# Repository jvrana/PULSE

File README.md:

# PULSE

## Opensource LED pulser for optogenetic applications

This repo provides instructions for building an inexpensive and open-sourced LED pulser for optogenetic applications. The pulser is a multi-output, programmable LED light device. 

IMAGE OF INTERFACE

IMAGE OF IT IN ACTION

IMAGE OF IT BEING BUILT

Service: ...message about contact...

/*
 @author: Justin D Vrana
 @version v2.32
 @since 2014-04-03

What is this?
The basic code needed to control a multi-output, programmable LED light device for optogenetic applications. 
The the code allows for user-defined parameters to alter duration and intensity of light pulses at regular intervals.  
Central to the device is an inexpensive microcontroller and LCD keypad to display and read user input to control 
the duration and intensity of LED light pulses at user-defined intervals. Up to three LED outputs can be independently
programmed and different LED modules can be interchanged.

Usage:
Upload to Arduino Uno via USB. If uploaded properly, "Starting" should display on the LCD display screen and then the main page should display.
If there are issue uploading to the Arduino Uno, consult the Arduino website for help.
    
    To turn an output ON or OFF: From the main page on the LCD display, use the UP and DOWN buttons to select an output (indicated by a cursor)
    to edit. Move the cursor to the right using the RIGHT button and use either the UP or DOWN button to turn the output program ON
    or OFF. A countdown timer which counts down untill the next time the LED is to flash will display when the output program is running. 
    
    To change an output's scheduled flashing: To change an output program, push SELECT to select the output highlighted by the cursor. 
    Use the UP and DOWN buttons to select and attribute to edit. To edit and attribute, move the cursor to the right using the RIGHT
    button and then hold the UP or DOWN button to increase or decease a value. Move the cursor back to the left using the LEFT button 
    to change attributes to edit. Push the SELECT button at any time to return to the main page.

Sources:
- The original "LiquidCrystal" 8-bit library and tutorial
    http://www.arduino.cc/en/uploads/Tutorial/LiquidCrystal.zip
    http://www.arduino.cc/en/Tutorial/LCDLibrary

Tested only with a Arduino Uno (http://arduino.cc/) and DFRobot Keypad Shield (http://dfrobot.com)

*****Important*****:
Check and change "User Defined Paramters" directly below if needed. LCD pins, output pins, and anaolog voltages
must be changed if using an LCD Keypad Shield other than the DFRobot Keypad Shield or SainSmart Keypad Shield.
Refer to the datasheet of the LCD Keypad Shield to determine correct parameter values. 
Button values can be reset for using the "Button Reset Mode"

Button Reset Mode:
If using a different LCD Keypad shield, button values may need to be reset. To initiate button reset mode, during startup hold
down any button and continue holding button for at least three seconds when prompted. Follow the on screen instructions.
The screen will request you press and hold each button while it records the voltage values associated with that button.
Once completed, voltage values will be stored to the Arduino's EEPROM memory. Upon each start-up, these voltage values
will be loaded and used. To reset button values on the Arduino, simply re-upload this program using the "UPLOAD" button.

V 2.0 - New Version with new interface
V 2.1 - Re-vamped interface
V 2.2 - Expanded to three outputs
V2.3 - Created button reset mode
V2.32 (4/10/14) - Corrected coding error, cast timers to int instead of long
*/

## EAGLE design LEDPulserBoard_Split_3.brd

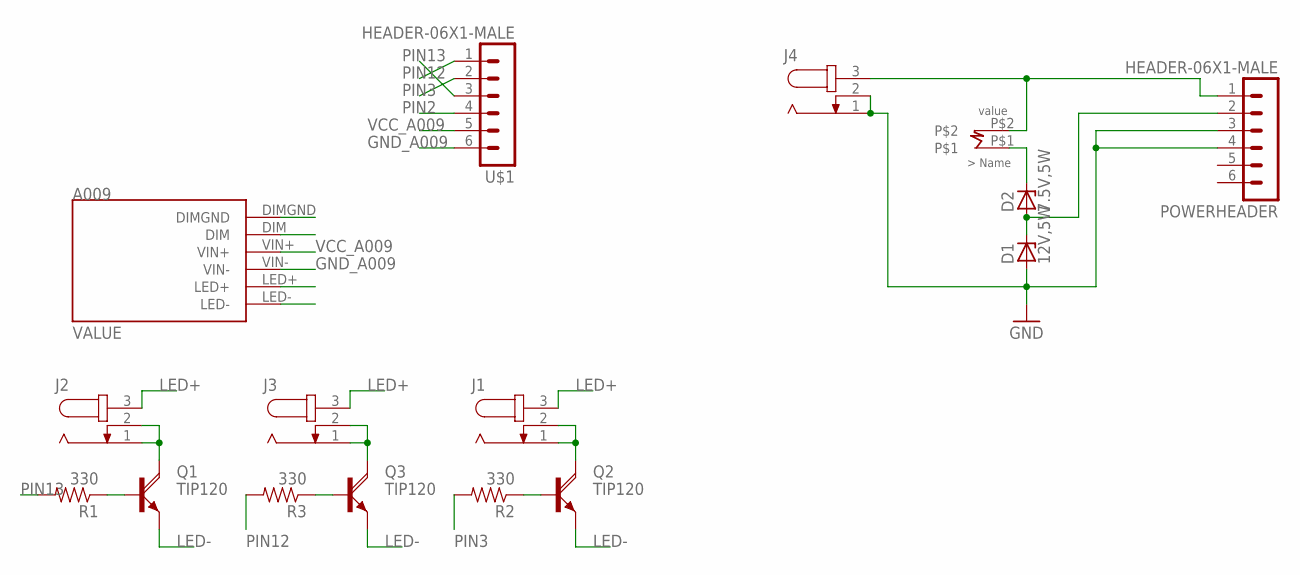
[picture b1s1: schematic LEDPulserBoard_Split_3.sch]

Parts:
D1: 12V,5W; C1702-15
D2: 7.5V,5W; C1702-15
J1, J2, J3, J4: JACK-PLUG0; SPC4077
POWERHEADER: HEADER-06X1-MALE; 06X1-PTH
Q1, Q2, Q3: TIP120; TO220AH
R1, R2, R3: 330; AXIAL-0.4
U$1: HEADER-06X1-MALE; 06X1-PTH
U$2: BUCKBLOCKA009; BUCKBLOCK
U$3: 5WRES; 5WAXIAL

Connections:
ARDUINOIN: D1.C, D2.A, POWERHEADER.2
DIM: U$2.DIM
DIMGND: U$2.DIMGND
GND: D1.A, J4.1, J4.2, POWERHEADER.3, POWERHEADER.4
GND_A009: U$1.6, U$2.VIN-
LED+: J1.3, J2.3, J3.3, U$2.LED+
LED-: Q1.E, Q2.E, Q3.E, U$2.LED-
unnamed: J1.1, J1.2, Q2.C
unnamed: Q2.B, R2.P$1 (1)
unnamed: J2.1, J2.2, Q1.C
unnamed: Q1.B, R1.P$1 (1)
unnamed: J3.1, J3.2, Q3.C
unnamed: Q3.B, R3.P$1 (1)
unnamed: D2.C, U$3.P$1
PIN2: U$1.4
PIN3: R2.P$2 (2), U$1.2
PIN12: R3.P$2 (2), U$1.1
PIN13: R1.P$2 (2), U$1.3
VCC: J4.3, POWERHEADER.1, U$3.P$2
VCC_A009: U$1.5, U$2.VIN+

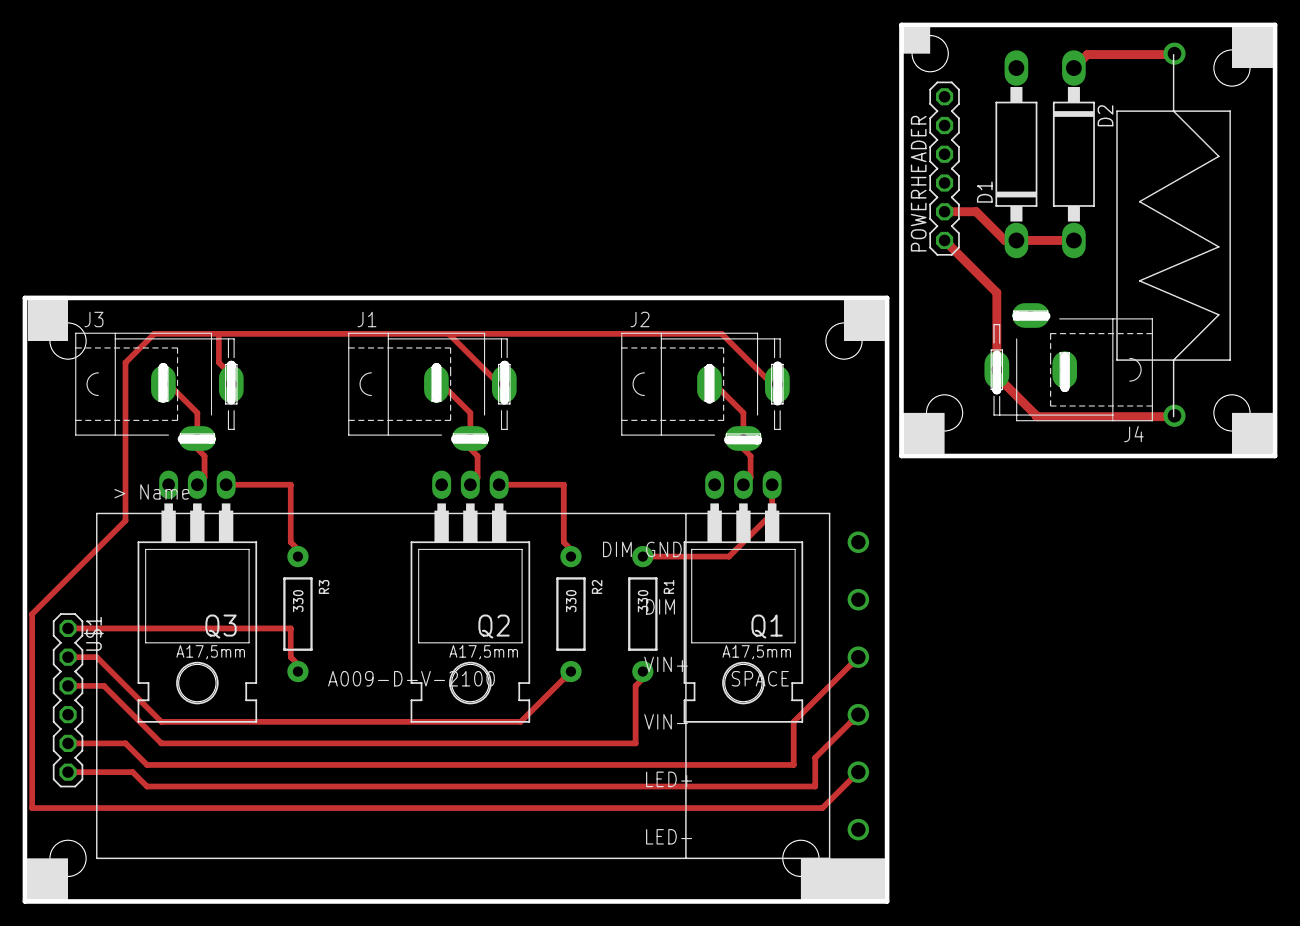
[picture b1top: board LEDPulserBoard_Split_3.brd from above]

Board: 2 copper layers, 110.1 x 77.1 mm, 16 parts (0 on the bottom side), 17 nets.

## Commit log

2016-06-27 init
2016-06-27 readme

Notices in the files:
parts and their libraries:
GeekAmmo: Licensing:Creative Commons ShareAlike 4.0 International - https://creativecommons.org/licenses/by-sa/4.0
